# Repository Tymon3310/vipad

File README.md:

# vipad
vipad is a 4x4 macropad powered by vial firmware

It also has 2 encoders (knobs), oled screen and rgb leds

Overall render:

Schematics:

PCB:

Bill of materials:
- 1 custom pcb
- 16 MX-style mechanical switches
- 16 Blank DSA keycaps
- 2 EC11 rotary encoders
- 1 0.91” 128×32 OLED display
- 1 case (top and bottom)
- 1 Seeed XIAO RP2040
- 22 1N4148 diodes
- 5 SK6812 MINI-E RGB LEDs
- 6 M3×16mm screws
- 6 M3×5×4mm heatset inserts

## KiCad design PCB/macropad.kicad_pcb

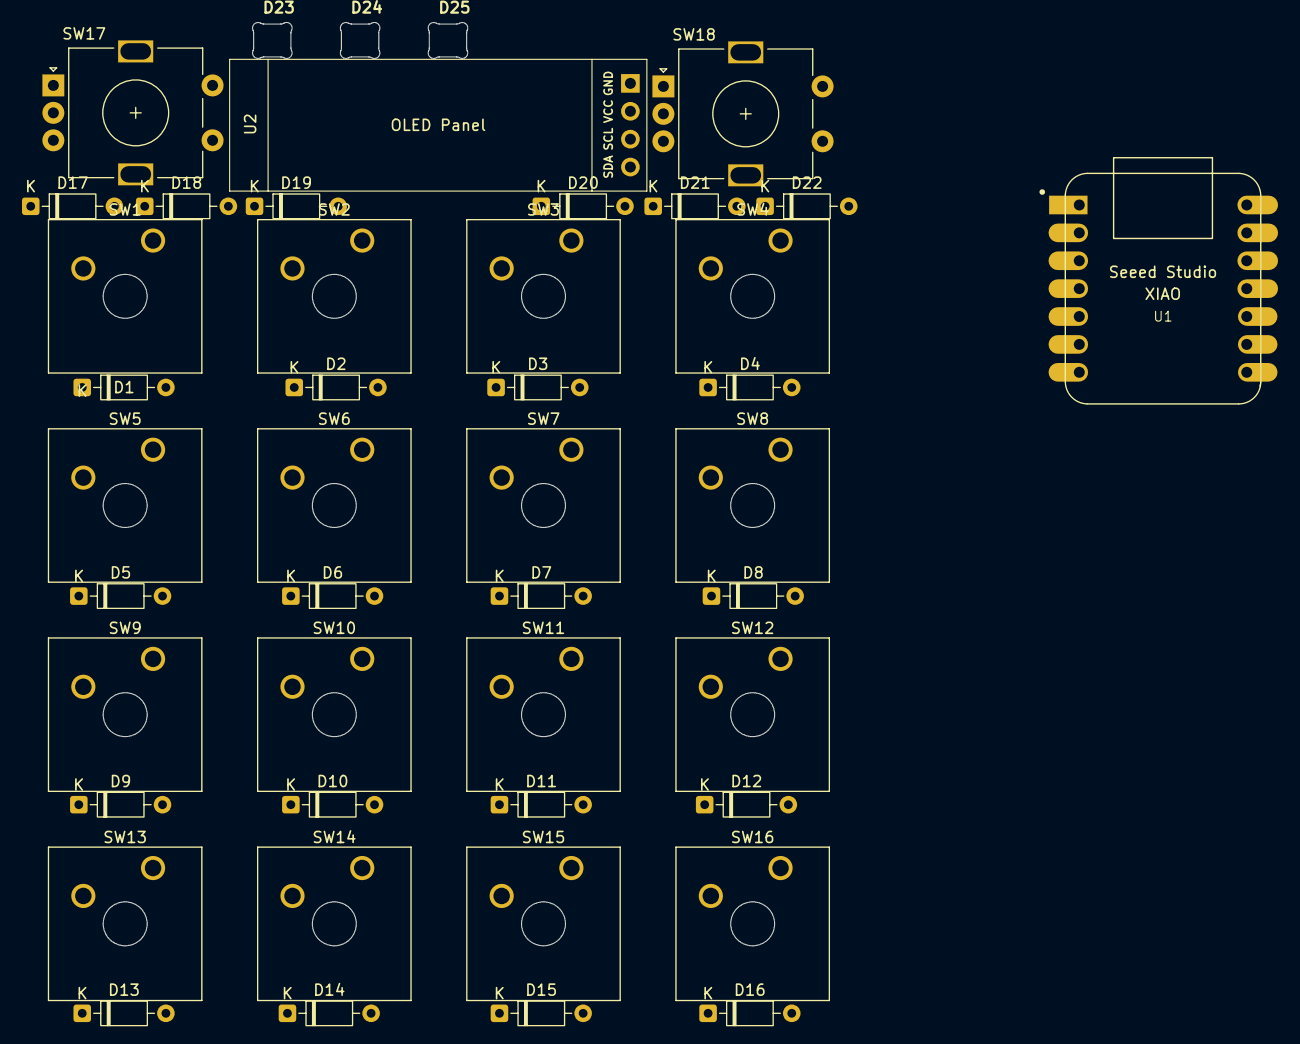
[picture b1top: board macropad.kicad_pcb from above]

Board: 2 copper layers, 45 parts (0 on the bottom side), 32 nets, no tracks yet.

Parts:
D1, D2, D3, D4, D5, D6, D7, D8, D9, D10, D11, D12, D13, D14, D15, D16, D17, D18, D19, D20, D21, D22: 1N4148; D_DO-35_SOD27_P7.62mm_Horizontal
D23, D24, D25: SK6812MINI-E; SK6812MINI-E_fixed
SW1, SW2, SW3, SW4, SW5, SW6, SW7, SW8, SW9, SW10, SW11, SW12, SW13, SW14, SW15, SW16: SW_Push; SW_Cherry_MX_1.00u_Plate
SW17, SW18: RotaryEncoder_Switch; RotaryEncoder_Alps_EC11E-Switch_Vertical_H20mm
U1: MOUDLE-SEEEDUINO-XIAO; XIAO-Generic-Hybrid-14P-2.54-21X17.8MM
U2: ER_OLEDM0.91_1x-I2C; SSD1306-0.91-OLED-4pin-128x32

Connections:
/3.3V: U1.12 (3V3), U2.2 (VCC)
/5V: D23.1 (VDD), D24.1 (VDD), D25.1 (VDD), U1.14 (5V)
/COL0: D17.2 (A), D18.2 (A), SW1.1, SW5.1, SW9.1, SW13.1, SW17.A, SW17.B, SW18.S1, U1.7 (PB08_A6_D6_TX)
/COL1: D20.2 (A), D21.2 (A), SW2.1, SW6.1, SW10.1, SW14.1, SW17.S1, SW18.A, SW18.B, U1.8 (PB09_A7_D7_RX)
/COL2: SW3.1, SW7.1, SW11.1, SW15.1, U1.9 (PA7_A8_D8_SCK)
/COL3: SW4.1, SW8.1, SW12.1, SW16.1, U1.10 (PA5_A9_D9_MISO)
/RGB_DATA: D23.4 (DIN), U1.11 (PA6_A10_D10_MOSI)
/ROW0: D1.1 (K), D2.1 (K), D3.1 (K), D4.1 (K), D17.1 (K), D20.1 (K), U1.1 (PA02_A0_D0)
/ROW1: D5.1 (K), D6.1 (K), D7.1 (K), D8.1 (K), D18.1 (K), D21.1 (K), U1.2 (PA4_A1_D1)
/ROW2: D9.1 (K), D10.1 (K), D11.1 (K), D12.1 (K), D19.2 (A), U1.3 (PA10_A2_D2)
/ROW3: D13.1 (K), D14.1 (K), D15.1 (K), D16.1 (K), D22.2 (A), U1.4 (PA11_A3_D3)
/SCL: U1.6 (PA9_A5_D5_SCL), U2.3 (SCL)
/SDA: U1.5 (PA8_A4_D4_SDA), U2.4 (SDA)
GND: D23.3 (VSS), D24.3 (VSS), D25.3 (VSS), SW17.C, SW18.C, U1.13 (GND), U2.1 (GND)
unnamed: D1.2 (A), SW1.2
unnamed: D2.2 (A), SW2.2
unnamed: D3.2 (A), SW3.2
unnamed: D4.2 (A), SW4.2
unnamed: D5.2 (A), SW5.2
unnamed: D6.2 (A), SW6.2
unnamed: D7.2 (A), SW7.2
unnamed: D8.2 (A), SW8.2
unnamed: D9.2 (A), SW9.2
unnamed: D10.2 (A), SW10.2
unnamed: D11.2 (A), SW11.2
unnamed: D12.2 (A), SW12.2
unnamed: D13.2 (A), SW13.2
unnamed: D14.2 (A), SW14.2
unnamed: D15.2 (A), SW15.2
unnamed: D16.2 (A), SW16.2
unnamed: D19.1 (K), SW17.S2
unnamed: D22.1 (K), SW18.S2

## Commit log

2026-06-06 push
2026-06-07 update fw
